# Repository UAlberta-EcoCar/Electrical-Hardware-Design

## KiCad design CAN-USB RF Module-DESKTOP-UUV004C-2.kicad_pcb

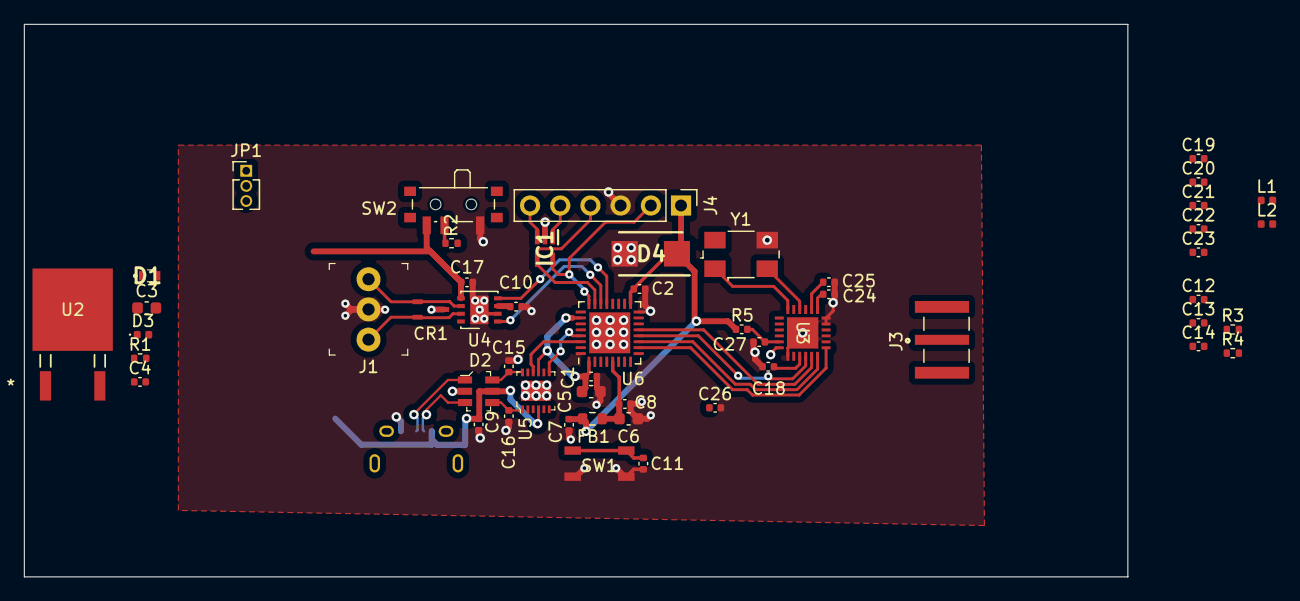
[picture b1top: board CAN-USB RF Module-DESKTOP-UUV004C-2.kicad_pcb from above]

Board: 2 copper layers, 92.8 x 46.5 mm, 54 parts (1 on the bottom side), 32 nets.

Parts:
C1, C2, C4, C9, C10, C11, C12, C14, C17, C18, C27: 100n; C_0402_1005Metric
C3: 22u; C_0603_1608Metric
C5: 10u; C_0603_1608Metric
C6: 1u; C_0603_1608Metric
C7: 1u; C_0402_1005Metric
C8, C24, C25: 10n; C_0402_1005Metric
C13: 4u7; C_0402_1005Metric
C15, C16: 47p; C_0402_1005Metric
C19: 0.8p; C_0402_1005Metric
C20, C23: 1p2; C_0402_1005Metric
C21: 0.5p; C_0402_1005Metric
C22: 100p; C_0402_1005Metric
C26: 470n; C_0402_1005Metric
CR1: ESDCAN03-2BWY; SOT323-3L_STM
D1: ESDA7P120-1U1M; ESDA8P801U1M
D2: USBLC6-2SC6; SOT23-6L
D3: RED; LED_0402_1005Metric
D4: SMLVT3V3; DIOM5436X265N
FB1: 120R; R_0603_1608Metric
IC1: ESDALC6V1W5; SOT65P210X110-5N
J1: 0022232031; PinHeader_1x3_P2.54mm_Drill1.02mm
J2: USB_B_Micro; USB_Micro-B_Amphenol_10118194_Horizontal
J3: Conn_Coaxial; TAOGLAS_EMPCB.SMAFSTJ.B.HT
J4: Conn_01x06_Pin; PinHeader_1x06_P2.54mm_Vertical
JP1: Jumper_3_Bridged12; PinHeader_1x03_P1.27mm_Vertical
L1: 3n; L_0402_1005Metric
L2: 2n5; L_0402_1005Metric
R1: 1k5; R_0402_1005Metric
R2: 10k; R_0402_1005Metric
R3, R4: 27R; R_0402_1005Metric
R5: 0R; C_0402_1005Metric
SW1: RESET; SMD_025816_WRE
SW2: BOOT0; SW_SPDT_PCM12
U2: TLV2217-33KVURG3; KVU3_TEX
U3: SX1280IMLTRT; QFN24_4X4_SEM
U4: MCP2542WFDxMF (CAN); DFN-8-1EP_3x3mm_P0.65mm_EP1.55x2.4mm
U5: FT234XD-R; DFN-12-1EP_3x3mm
U6: STM32L442KCU6; QFN-32-1EP_5x5mm_P0.5mm_EP3.45x3.45mm
Y1: 52MHz; Crystal_SMD_0603-4Pin_6.0x3.5mm

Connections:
+3.3V: C3.1, U2.1 (OUTPUT)
+3.3VA: C6.1, C8.1, FB1.1, U6.5 (VDDA)
+3V3: C1.1, C2.1, C5.1, C7.1, C12.1, C17.2, C18.1, D4.1 (K), FB1.2, IC1.3 (I/02), J4.1, J4.6, R5.2, SW2.3 (C), U3.15 (VBAT), U4.5 (VIO), U5.9 (VCCIO), U6.1 (VDD), U6.17 (VDD), U6.26 (PB3)
+5V: C4.1, C10.2, D1.1 (K), D3.2 (A), JP1.1 (A), JP1.2 (C), U2.3 (INPUT), U4.3 (VDD)
/BOOT0: R2.1, R2.2, SW2.2 (B), U6.31 (PH3)
/CAN Tranciever/CANH+: CR1.2, J1.1, U4.7 (CANH)
/CAN Tranciever/CANL-: CR1.1, J1.3, U4.6 (CANL)
/CAN_RX: U4.4 (RXD), U6.21 (PA11)
/CAN_TX: U4.1 (TXD), U6.22 (PA12)
/DEBUG_JTSK_SWCLK: IC1.5 (I/04), J4.2, U6.24 (PA14)
/DEBUG_JTSK_SWDIO: IC1.4 (I/03), J4.4, U6.23 (PA13)
/LoRa Tranciever/V DIO: C27.1, R5.1, U3.11 (VBAT_IO)
/NRST: C11.2, IC1.1 (I/01), J4.5, SW1.3 (K), SW1.4 (A), U6.4 (NRST)
/SPI1_MISO: U3.16 (MISO_TX), U6.12 (PA6)
/SPI1_MOSI: U3.17 (MOSI_RX), U6.13 (PA7)
/SPI1_NSS: U3.19 (NSS_CTS), U6.10 (PA4)
/SPI1_SCK: U3.18 (SCK_RTSN), U6.11 (PA5)
/UART1_USB_RX: U5.10 (RXD), U6.30 (PB7)
/UART1_USB_TX: U5.7 (TXD), U6.29 (PB6)
/USB Interface/USB_D+: C15.2, D2.1, D2.6, J2.3 (D+), R3.1, R3.2, U5.12 (USBDP)
/USB Interface/USB_D-: C16.2, D2.3, D2.4, J2.2 (D-), R4.1, R4.2, U5.1 (USBDM)
GND: C1.2, C2.2, C3.2, C4.2, C5.2, C6.2, C7.2, C8.2, C9.1, C10.1, C11.1, C12.2, C13.2, C14.2, C15.1, C16.1, C17.1, C18.2, C19.1, C20.2, C23.1, C24.2, C25.2, C26.2, C27.2, CR1.3, D1.2 (A), D2.2, D4.2 (A), IC1.2 (GND), J1.2, J2.5 (GND), J4.3, R1.1, SW1.1, SW1.2, SW2.1 (A), U2.2 (GND), U3.5 (GND), U3.13 (GND), U3.20 (GND), U3.21 (GND), U3.23 (GND), U3.24 (GND), U3.25 (GND), U4.2 (VSS), U4.9 (VSS), U5.5 (GND), U5.13 (GND), U6.16 (VSS), U6.32 (VSS), U6.33 (VSS), Y1.3
unnamed: C20.1, C21.1, L1.2, L2.1
unnamed: C21.2, C22.1, C23.2, L2.2
unnamed: D3.1 (K), R1.2
unnamed: C22.2, J3.1 (In)
unnamed: C25.1, C26.1, U3.2 (VDD_INN), U3.12 (DCC_FB)
unnamed: C19.2, L1.1, U3.22 (RFIO)
unnamed: C24.1, U3.1 (VR_PA)
unnamed: U3.4 (XTA), Y1.2
unnamed: U3.6 (XTB), Y1.1
VBUS: C9.2, C13.1, C14.1, D2.5, J2.1 (VBUS), JP1.3 (B), U5.4 (VCC)

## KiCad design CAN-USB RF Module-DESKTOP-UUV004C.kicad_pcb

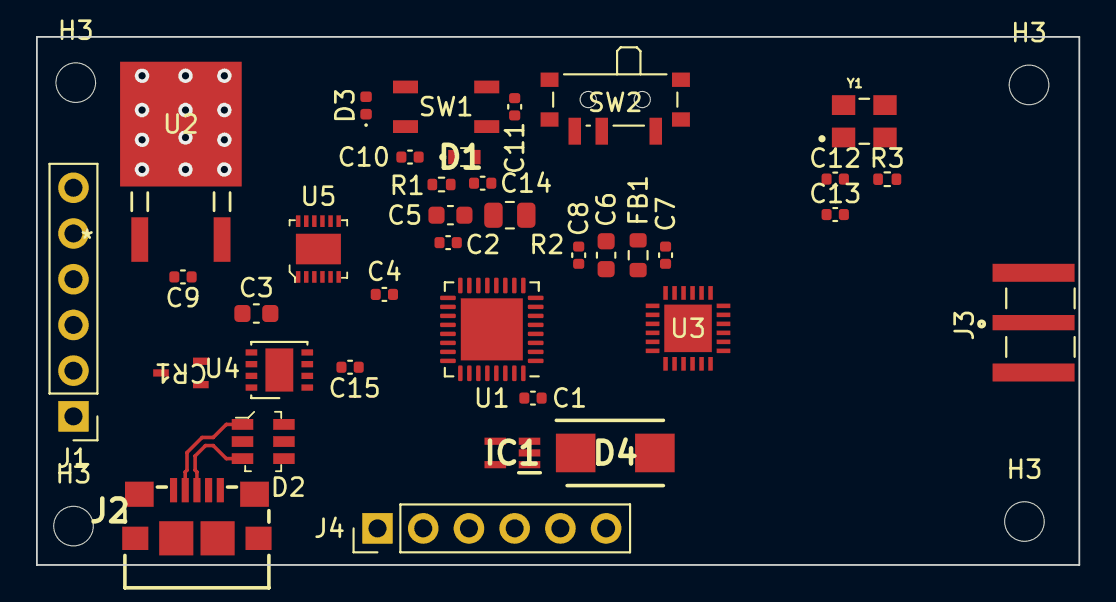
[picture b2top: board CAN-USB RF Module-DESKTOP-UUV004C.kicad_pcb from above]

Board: 2 copper layers, 57.9 x 29.3 mm, 41 parts (0 on the bottom side), 20 nets.

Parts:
C1, C2, C4, C9, C10, C11, C14: 100n; C_0402_1005Metric
C3: 22u; C_0603_1608Metric
C5: 10u; C_0603_1608Metric
C6: 1u; C_0603_1608Metric
C7: 1u; C_0402_1005Metric
C8: 10n; C_0402_1005Metric
C12, C13: 14p; C_0402_1005Metric
C15: 100u; C_0402_1005Metric
CR1: ESDCAN03-2BWY; SOT323-3L_STM
D1: ESDA7P120-1U1M; ESDA8P801U1M
D2: USBLC6-2SC6; SOT23-6L
D3: RED; LED_0402_1005Metric
D4: SMLVT3V3; DIOM5436X265N
FB1: 120R; R_0603_1608Metric
H3, H3#2, H3#3, H3#4: MountingHole; MountingHole_2.2mm_M2_DIN965
IC1: ESDALC6V1W5; SOT65P210X110-5N
J1, J4: Conn_01x06_Pin; PinHeader_1x06_P2.54mm_Vertical
J2: USB_B_Micro; 1981568-1
J3: Conn_Coaxial; TAOGLAS_EMPCB.SMAFSTJ.B.HT
R1: 1k5; R_0402_1005Metric
R2: 10k; R_0805_2012Metric
R3: 390; R_0402_1005Metric
SW1: RESET; SMD_025816_WRE
SW2: BOOT0; SW_SPDT_PCM12
U1: STM32L442KCUx; QFN-32-1EP_5x5mm_P0.5mm_EP3.45x3.45mm
U2: TLV2217-33KVURG3; KVU3_TEX
U3: SX1280IMLTRT; QFN24_4X4_SEM
U4: MCP2542WFDxMF (CAN); DFN-8-1EP_3x3mm_P0.65mm_EP1.55x2.4mm
U5: FT234XD-R; DFN-12-1EP_3x3mm
Y1: 8 MHz; XTAL_ECS-240-8-33-AGN-TR

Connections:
+3.3V: C1.1, C2.1, C3.1, C5.1, C7.1, C15.2, D4.1 (K), FB1.2, J4.1, SW2.3 (C), U1.1 (VDD), U1.17 (VDD), U2.1 (OUTPUT), U4.3 (VDD), U4.5 (VIO)
+3.3VA: C6.1, C8.1, FB1.1, U1.5 (VDDA)
/BOOT0: R2.1, R2.2, SW2.2 (B), U1.31 (PH3)
/CAN_RX: U1.21 (PA11), U4.4 (RXD)
/CAN_TX: U1.22 (PA12), U4.1 (TXD)
/DEBUG_JTDO-SWO: IC1.3 (I/02), J4.6
/DEBUG_JTSK_SWCLK: IC1.5 (I/04), J4.2, U1.24 (PA14)
/DEBUG_JTSK_SWDIO: IC1.4 (I/03), J4.4, U1.23 (PA13)
/NRST: C11.2, IC1.1 (I/01), J4.5, SW1.3 (K), SW1.4 (A), U1.4 (NRST)
/USART1_RX: U1.30 (PB7), U5.10 (RXD)
/USART1_TX: U1.29 (PB6), U5.7 (TXD)
/USB Interface/USB_D+_C: D2.3, J2.3 (D+)
/USB Interface/USB_D-_C: D2.1, J2.2 (D-)
GND: C1.2, C2.2, C3.2, C4.2, C5.2, C6.2, C7.2, C8.2, C9.1, C10.2, C11.1, C12.2, C13.2, C14.1, C15.1, CR1.3, D1.2 (A), D2.2, D4.2 (A), IC1.2 (GND), J1.6, J4.3, R1.1, SW1.1, SW1.2, SW2.1 (A), U1.16 (VSS), U1.32 (VSS), U1.33 (VSS), U2.2 (GND), U4.2 (VSS), U4.9 (VSS), U5.5 (GND), U5.13 (GND), Y1.2, Y1.3
unnamed: C12.1, R3.1, Y1.4
unnamed: D3.1 (K), R1.2
unnamed: CR1.2, J1.2, U4.7 (CANH)
unnamed: CR1.1, J1.4, U4.6 (CANL)
RCC_OSC_IN: C13.1, Y1.1
VBUS: C4.1, C9.2, C10.1, C14.2, D1.1 (K), D2.5, D3.2 (A), J2.4 (ID), U2.3 (INPUT)

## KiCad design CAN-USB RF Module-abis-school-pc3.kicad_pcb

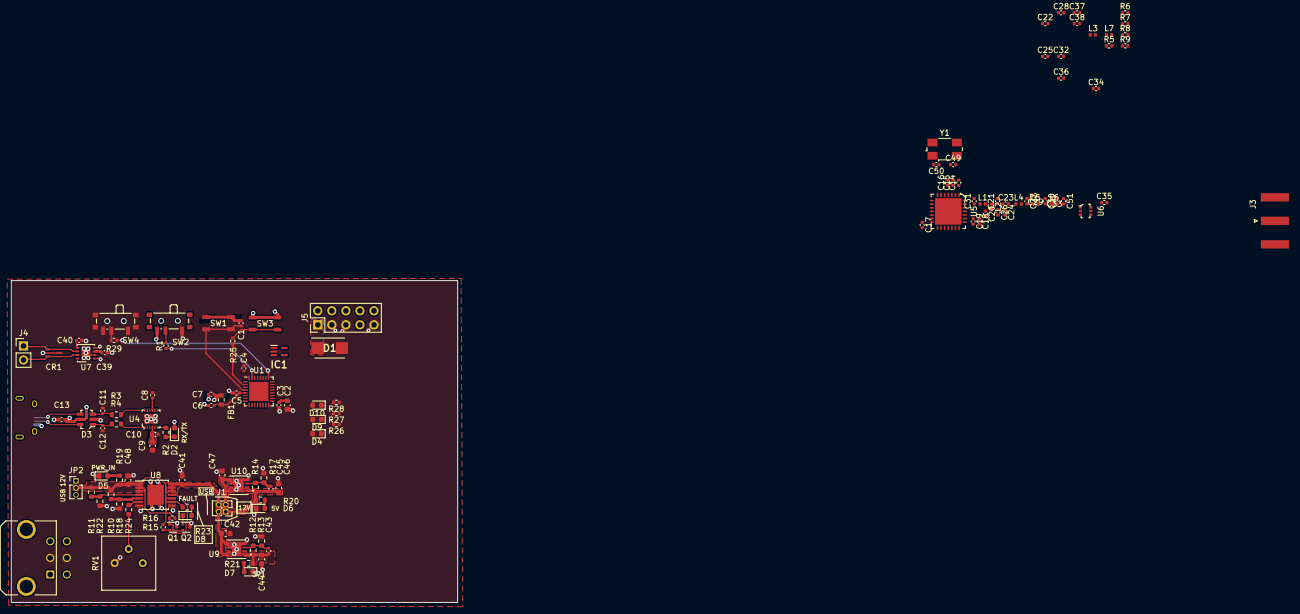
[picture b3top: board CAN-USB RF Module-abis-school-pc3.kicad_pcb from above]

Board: 4 copper layers, 80.6 x 58.2 mm, 123 parts (1 on the bottom side), 81 nets.

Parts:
C1, C3, C4, C8, C10, C13, C14, C15, C16, C17, C19, C39, C40: 100n; C_0402_1005Metric
C2, C48: 10u; C_0603_1608Metric
C5, C20, C31: 10n; C_0402_1005Metric
C6, C7: 1u; C_0402_1005Metric
C9: 4u7; C_0603_1608Metric
C11, C12, C18, C24, C26, C28, C32, C36: 47p; C_0402_1005Metric
C21: 8p2; C_0402_1005Metric
C22, C29, C33, C37, C38, C51: NC; C_0402_1005Metric
C23: 22p; C_0402_1005Metric
C25, C30: 3p3; C_0402_1005Metric
C27: 6p8; C_0402_1005Metric
C34, C35: 1n; C_0402_1005Metric
C41, C42, C47: 1u; C_0603_1608Metric
C43, C45: 10p; C_0402_1005Metric
C44, C46: 2u2; C_0603_1608Metric
C49, C50: 8p; C_0402_1005Metric
CR1: ESDCAN03-2BWY; SOT323-3L_STM
D1: SMLVT3V3; DIOM5436X265N
D2: AMBER RX/TX; LED_0603_1608Metric
D3: USBLC6-2SC6; SOT23-6L
D4, D9: AMBER; LED_0603_1608Metric
D5, D6, D7: BLUE; LED_0603_1608Metric
D8: RED; LED_0603_1608Metric
D10: GREEN; LED_0603_1608Metric
FB1: 120R; R_0603_1608Metric
IC1: ESDALC6V1W5; SOT65P210X110-5N
J1: USB JMPR; PinHeader_2x02_P1.27mm_Vertical
J2: USB_B_Micro; USB_Micro-B_Amphenol_10118194_Horizontal
J3: Conn_Coaxial; SMA_Amphenol_132289_EdgeMount
J4: Conn_01x02_Socket; PinHeader_1x02_P2.54mm_Vertical
J5: Conn_02x05_Top_Bottom; PinHeader_2x05_P2.54mm_Vertical
J6: Fuel Cell Connector; Molex_Micro-Fit_3.0_43045-0621_2x03-1MP_P3.00mm_Horizontal
JP2: Power In; PinHeader_1x03_P1.27mm_Vertical
L1: 1n5; L_0402_1005Metric
L2: 33n; L_0402_1005Metric
L3: 10n; L_0402_1005Metric
L4, L5: 5n6; L_0402_1005Metric
L6, L7: 0H; L_0402_1005Metric
Q1, Q2: NMOS; SOT-523
R1, R15, R16, R25, R26, R27, R28, R29: 10k; R_0402_1005Metric
R2, R21: 260R; R_0603_1608Metric
R3, R4: 27R; R_0603_1608Metric
R5: 0R; R_0402_1005Metric
R6: 100R; R_0402_1005Metric
R7, R9: NC; R_0402_1005Metric
R8: 1k; R_0402_1005Metric
R10, R11: 2M2; R_0603_1608Metric
R12: 500k; R_0603_1608Metric
R13, R17: 160k; R_0603_1608Metric
R14: 845k; R_0603_1608Metric
R18: 225k; R_0603_1608Metric
R19, R20, R23: 600R; R_0603_1608Metric
R22: 800k; R_0603_1608Metric
R24: 10k; R_0603_1608Metric
RV1: SETI; Potentiometer_Bourns_3386P_Vertical
SW1: RESET; SMD_025816_WRE
SW2: BOOT0; SW_SPDT_PCM12
SW3: GPBTN; SMD_025816_WRE
SW4: GPSW; SW_SPDT_PCM12
U1: STM32L442KCU6; QFN-32-1EP_5x5mm_P0.5mm_EP3.45x3.45mm
U4: FT234XD-R; DFN-12-1EP_3x3mm
U5: SX1276IMLTRT; VQFN-28-1EP_6x6mm
U6: P4259-63; SOT-363
U7: MCP2542WFDxMF (CAN); DFN-8-1EP_3x3mm_P0.65mm_EP1.55x2.4mm
U8: MAX14572; TSSOP-14-1EP_4.4x5mm_P0.65mm
U9, U10: TLV76601QWDRBRQ1; TLV76601QWDRBRQ1_TEX
Y1: 32MHz; Crystal_SMD_0603-4Pin_6.0x3.5mm

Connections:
+3.3VA: C5.1, C6.1, FB1.1, U1.5 (VDDA)
+3V3: C2.1, C3.1, C4.1, C7.1, C8.1, C15.1, C17.1, C18.1, C19.1, C34.1, C40.2, C43.1, C44.1, D1.1 (K), D2.2 (A), FB1.2, J5.1, R8.2, R12.1, R21.1, SW2.3 (C), SW3.1, SW3.2, SW4.3 (C), U1.1 (VDD), U1.17 (VDD), U4.9 (VCCIO), U5.3 (VBAT_ANA), U5.14 (VBAT_DIG), U5.24 (VBAT_RF), U6.6 (~CTRL/VDD), U7.5 (VIO), U9.1 (OUT)
+5V: C9.1, C10.1, C39.2, C45.1, C46.1, J1.1, R14.1, R20.1, U4.4 (VCC), U7.3 (VDD), U10.1 (OUT)
+12V: J6.1, J6.4, JP2.3 (B)
/BOOT0: R1.1, R1.2, SW2.2 (B), U1.31 (PH3)
/CAN Tranciever/CANH+: CR1.2, J4.2, U7.7 (CANH)
/CAN Tranciever/CANL-: CR1.1, J4.1, U7.6 (CANL)
/CAN_RX: U1.21 (PA11), U7.4 (RXD)
/CAN_STBY: U1.3 (PC15), U7.8 (STBY)
/CAN_TX: U1.22 (PA12), U7.1 (TXD)
/DEBUG_SWCLK: IC1.4 (I/03), J5.4, U1.24 (PA14)
/DEBUG_SWDIO: IC1.5 (I/04), J5.2, U1.23 (PA13)
/DEBUG_SWO: IC1.3 (I/02), J5.6, U1.26 (PB3)
/DIO0: U1.14 (PB0), U5.8 (DIO0)
/DIO1: U1.15 (PB1), U5.9 (DIO1/DCLK)
/DIO2: U1.29 (PB6), U5.10 (DIO2/DATA)
/DIO3: U1.30 (PB7), U5.11 (DIO3), U5.12 (DIO4), U5.13 (DIO5)
/LoRa Tranciever/RFI_HF: C22.1, L3.1, U5.21 (RFI_HF(GND))
/LoRa Tranciever/RXTX_SW: C35.1, R6.1, R7.1, U6.4 (CTRL)
/LoRa Tranciever/RXTX_SX: R7.2, U5.20 (RXTX/RF_MOD)
/NRST: C1.2, IC1.1 (I/01), J5.10, SW1.3 (K), SW1.4 (A), U1.4 (NRST), U4.2 (RESET#)
/Power Regulator/5V: C42.1, J1.2, U9.5 (EN), U9.8 (IN)
/Power Regulator/12V: C47.1, J1.3, U10.5 (EN), U10.8 (IN)
/Power Regulator/FB: C43.2, C45.2, R12.2, R13.1, R14.2, R17.1, U9.3 (FB), U10.3 (FB)
/Power Regulator/FUSE_IN: C48.1, JP2.2 (C), R10.1, R11.1, R15.1, R16.1, R19.1, R23.1, U8.1 (IN), U8.2 (IN), U8.3 (IN), U8.9 (RIEN), U8.10 (EN)
/Power Regulator/FUSE_OUT: C41.1, J1.4, U8.12 (OUT), U8.13 (OUT), U8.14 (OUT)
/Power Regulator/OVLO: R10.2, R18.1, U8.5 (OVLO)
/Power Regulator/SETI: R24.1, U8.6 (SETI)
/Power Regulator/UVLO: R11.2, R22.1, U8.4 (UVLO)
/Power Regulator/~FLAG: Q1.2 (G), R15.2, U8.11 (~FLAG)
/SPI1_MISO: U1.12 (PA6), U5.17 (MISO)
/SPI1_MOSI: U1.13 (PA7), U5.18 (MOSI)
/SPI1_NSS: U1.10 (PA4), U5.19 (NSS)
/SPI1_SCK: U1.11 (PA5), U5.16 (SCK)
/SW_RXTX: R6.2, R8.1, R9.2, U1.27 (PB4)
/SX_RESET: U1.28 (PB5), U5.7 (NRESET)
/UART2_USB_CTS: U1.6 (PA0), U4.11 (CTS#)
/UART2_USB_RTS: U1.7 (PA1), U4.8 (RTS#)
/UART2_USB_RX: U1.9 (PA3), U4.10 (RXD)
/UART2_USB_TX: U1.8 (PA2), U4.7 (TXD)
/USB Interface/USB_D+: C11.2, D3.3, D3.4, J2.3 (D+), R3.1, R3.2, U4.12 (USBDP)
/USB Interface/USB_D-: C12.2, D3.1, D3.6, J2.2 (D-), R4.1, R4.2, U4.1 (USBDM)
GND: C1.1, C2.2, C3.2, C4.2, C5.2, C6.2, C7.2, C8.2, C9.2, C10.2, C11.1, C12.1, C13.1, C14.2, C15.2, C16.2, C17.2, C18.2, C19.2, C20.2, C21.2, C22.2, C24.2, C25.2, C26.2, C27.1, C30.1, C31.2, C34.2, C35.2, C37.1, C38.1, C39.1, C40.1, C41.2, C42.2, C44.2, C46.2, C47.2, C48.2, C49.2, C50.2, C51.1, CR1.3, D1.2 (A), D3.2, D4.1 (K), D5.1 (K), D6.1 (K), D7.1 (K), D9.1 (K), D10.1 (K), IC1.2 (GND), J2.5 (GND), J3.2 (Ext), J5.3, J5.5, J5.9, J6.2, J6.5, Q1.3 (S), Q2.3 (S), R9.1, R13.2, R17.2, R18.2, R22.2, RV1.3, SW1.1, SW1.2, SW2.1 (A), SW4.1 (A), U1.16 (VSS), U1.32 (VSS), U1.33 (VSS), U4.5 (GND), U4.13 (GND), U5.15 (GND), U5.23 (GND), U5.26 (GND), U5.29 (GND), U6.2 (GND), U7.2 (VSS), U7.9 (VSS), U8.7 (GND), U8.8 (~HVEN), U9.4 (GND), U9.6 (GND), U9.9 (GND), U10.4 (GND), U10.6 (GND), U10.9 (GND), Y1.2, Y1.4
unnamed: C21.1, C23.1, L1.2, L2.1
unnamed: C23.2, L4.1
unnamed: C25.1, C28.1, L3.2
unnamed: C27.2, C29.2, L4.2, L5.1
unnamed: C28.2, R5.1
unnamed: C29.1, C30.2, C33.2, L5.2, L6.1
unnamed: C32.1, R5.2
unnamed: C36.2, C37.2, L7.1
unnamed: D2.1 (K), R2.2
unnamed: D4.2 (A), R28.1
unnamed: D5.2 (A), R19.2
unnamed: D6.2 (A), R20.2
unnamed: D7.2 (A), R21.2
unnamed: D8.2 (A), R23.2
unnamed: D8.1 (K), Q2.1 (D)
unnamed: D9.2 (A), R27.1
unnamed: D10.2 (A), R26.1
unnamed: C38.2, J3.1 (In), L7.2
unnamed: Q1.1 (D), Q2.2 (G), R16.2
unnamed: R24.2, RV1.2
unnamed: R25.1, SW3.3 (K), SW3.4 (A)
unnamed: R29.1, SW4.2 (B)
unnamed: R28.2, U1.18 (PA8)
unnamed: R27.2, U1.19 (PA9)
unnamed: R26.2, U1.20 (PA10)
unnamed: R29.2, U1.25 (PA15)
unnamed: R25.2, U1.2 (PC14)
unnamed: R2.1, U4.6 (CBUS0)
unnamed: C31.1, L1.1, U5.27 (PA_BOOST)
unnamed: C14.1, U5.2 (VR_ANA)
unnamed: C16.1, U5.4 (VR_DIG)
unnamed: C20.1, C24.1, C26.1, L2.2, U5.25 (VR_PA)
unnamed: C49.1, U5.5 (XTA), Y1.3
unnamed: C50.1, U5.6 (XTB), Y1.1
unnamed: C32.2, U6.1 (RF1)
unnamed: C33.1, C51.2, L6.2, U6.3 (RF2)
unnamed: C36.1, U6.5 (RFC)
VBUS_UP: C13.2, D3.5, J2.1 (VBUS), JP2.1 (A)

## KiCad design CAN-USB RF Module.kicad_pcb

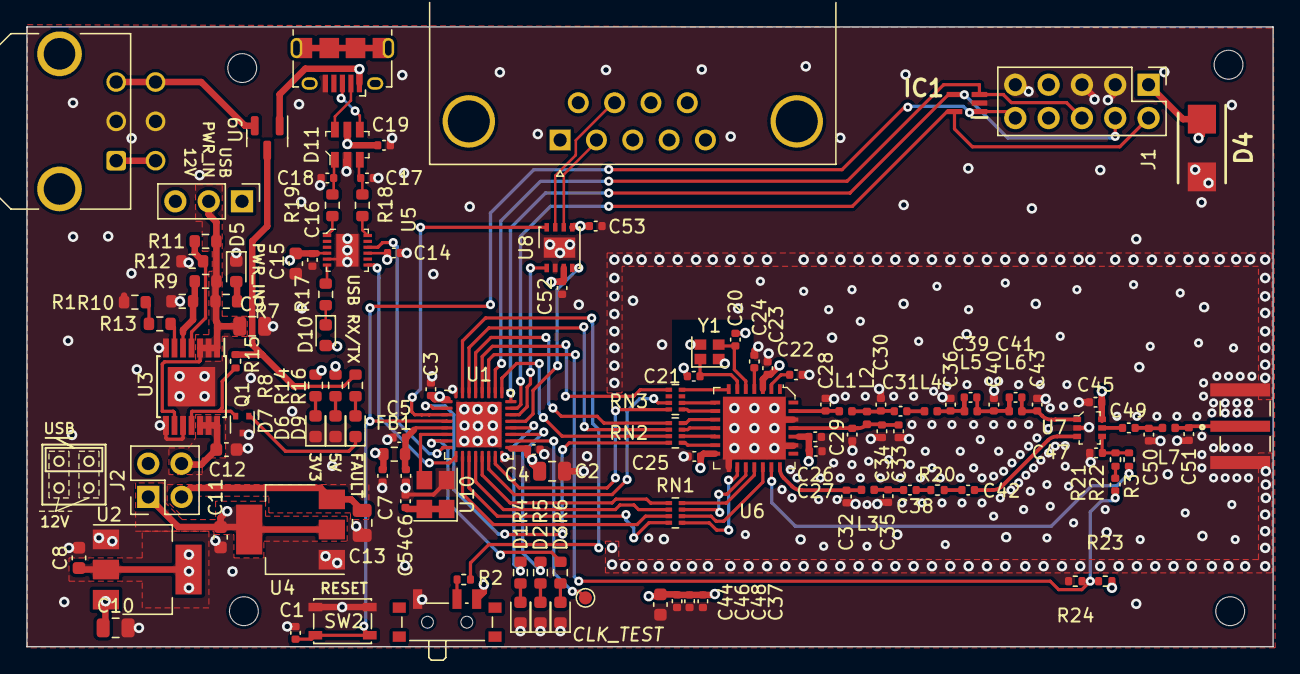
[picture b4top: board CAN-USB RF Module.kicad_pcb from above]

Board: 4 copper layers, 95.0 x 47.2 mm, 126 parts (0 on the bottom side), 91 nets.

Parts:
C1, C3, C4, C14, C16, C19, C22, C23, C24, C25, C27, C52, C53: 100n; C_0402_1005Metric
C2, C9, C10, C13: 10u; C_0805_2012Metric
C5, C28, C29: 10n; C_0402_1005Metric
C6, C7, C37, C46, C48: 1u; C_0402_1005Metric
C8, C11, C44: 22u; C_0603_1608Metric
C12: 1u; C_0603_1608Metric
C15: 4u7; C_0603_1608Metric
C17, C18, C26, C33, C34, C38, C42, C49: 47p; C_0402_1005Metric
C20, C21: 8p; C_0402_1005Metric
C30: 8p2; C_0402_1005Metric
C31: 22p; C_0402_1005Metric
C32, C39, C41, C43, C50, C51: NC; C_0402_1005Metric
C35, C40: 3p3; C_0402_1005Metric
C36: 6p8; C_0402_1005Metric
C45, C47: 1n; C_0402_1005Metric
C54: u1; C_0402_1005Metric
D1: GREEN; LED_0603_1608Metric
D2, D3, D10: AMBER; LED_0603_1608Metric
D4: SMLVT3V3; DIOM5436X265N
D5, D6, D7: BLUE; LED_0603_1608Metric
D9: RED; LED_0603_1608Metric
D11: USBLC6-2SC6; SOT23-6L
FB1: 120R; R_0603_1608Metric
H1, H2, H3, H4: MountingHole; MountingHole_2.2mm_M2
IC1: ESDALC6V1W5; SOT65P210X110-5N
J1: Conn_02x05_Top_Bottom; PinHeader_2x05_P2.54mm_Vertical
J2: USB JMPR; PinHeader_2x02_P2.54mm_Vertical
J3: Fuel Cell Connector; Molex_Micro-Fit_3.0_43045-0621_2x03-1MP_P3.00mm_Horizontal
J4: USB_B_Micro; USB_Micro-B_Amphenol_10118194_Horizontal
J5: Conn_Coaxial; TAOGLAS_EMPCB.SMAFSTJ.B.HT
J6: Conn_01x09_Socket; DSUB-9_Female_Horizontal_P2.77x2.84mm_EdgePinOffset7.70mm_H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
JP1: Power In; PinHeader_1x03_P2.54mm_Vertical
L1: 1n5; L_0402_1005Metric
L2: 33n; L_0402_1005Metric
L3: 10n; L_0402_1005Metric
L4, L5: 5n6; L_0402_1005Metric
L6, L7: 0H; L_0402_1005Metric
Q1: NMOS; SOT-523
R1: 1k5; R_0603_1608Metric
R2, R15: 10k; R_0402_1005Metric
R3: 100R; C_0402_1005Metric
R4, R5, R6: 110R; R_0603_1608Metric
R7, R14, R16: 600R; R_0603_1608Metric
R8, R17: 260R; R_0603_1608Metric
R9, R11: 2M2; R_0603_1608Metric
R10: 225k; R_0603_1608Metric
R12: 800k; R_0603_1608Metric
R13: 10k; R_0603_1608Metric
R18, R19: 27R; R_0603_1608Metric
R20: 0R; R_0402_1005Metric
R21: 100R; R_0402_1005Metric
R22, R24: NC; R_0402_1005Metric
R23: 1k; R_0402_1005Metric
RN1, RN2, RN3: 100R; R_Array_Concave_4x0402
SW2: RESET; SW_SPST_PTS810
SW3: BOOT0; SW_SPDT_PCM12
TP1: CLK_TEST; TestPoint_Pad_D1.0mm
U1: STM32L442KCU6; QFN-32-1EP_5x5mm_P0.5mm_EP3.45x3.45mm
U2: AZ1117-3.3; SOT-223-3_TabPin2
U3: MAX14572; TSSOP-14-1EP_4.4x5mm_P0.65mm
U4: AZ1117-5.0; SOT-223-3_TabPin2
U5: FT234XD-R; DFN-12-1EP_3x3mm
U6: SX1276IMLTRT; VQFN-28-1EP_6x6mm
U7: P4259-63; SOT-363
U8: MCP2542FDxMF; DFN-8-1EP_3x3mm_P0.65mm_EP1.55x2.4mm
U9: Common Cathode SBD; SOT-23
U10: 8MHz; Crystal_SMD_3225-4Pin_3.2x2.5mm
Y1: 32MHz; Crystal_SMD_2016-4Pin_2.0x1.6mm

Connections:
+3.3VA: C5.1, C6.1, FB1.1, U1.5 (VDDA)
+3V3: C2.1, C3.1, C4.1, C7.1, C8.1, C14.1, C23.1, C25.1, C26.1, C27.1, C37.1, C44.1, C45.1, C46.1, C48.1, C53.2, C54.2, D4.1 (K), D10.2 (A), FB1.2, J1.1, R8.1, R23.2, SW3.3 (C), U1.1 (VDD), U1.17 (VDD), U2.2 (VO), U5.9 (VCCIO), U6.3 (VBAT_ANA), U6.14 (VBAT_DIG), U6.24 (VBAT_RF), U7.6 (~CTRL/VDD), U8.5 (VIO), U10.1 (~ST), U10.4 (VCC)
+5V: C11.1, C15.1, C16.1, C52.2, J2.1, R14.1, U4.2 (VO), U5.4 (VCC), U8.3 (VDD)
+12V: J3.1, J3.4, JP1.3 (B)
/BOOT0: R2.1, R2.2, SW3.2 (B), U1.31 (PH3)
/CAN Tranciever/CD+: J6.7, U8.7 (CANH)
/CAN Tranciever/CD-: J6.2, U8.6 (CANL)
/CAN_RX: U1.21 (PA11), U8.4 (RXD)
/CAN_STBY: U1.3 (PC15), U8.8 (STBY)
/CAN_TX: U1.22 (PA12), U8.1 (TXD)
/DEBUG_SWCLK: IC1.4 (I/03), J1.4, U1.24 (PA14)
/DEBUG_SWDIO: IC1.5 (I/04), J1.2, U1.23 (PA13)
/DEBUG_SWO: IC1.3 (I/02), J1.6, U1.26 (PB3)
/DIO0: RN3.3 (R3.1), U1.14 (PB0)
/DIO1: RN3.4 (R4.1), U1.15 (PB1)
/DIO2: RN2.1 (R1.1), U1.29 (PB6)
/DIO3: RN2.2 (R2.1), U1.30 (PB7)
/DIO4: RN2.3 (R3.1), U1.25 (PA15)
/DIO5: RN2.4 (R4.1), U1.2 (PC14)
/LoRa Tranciever/DIO0: RN3.6 (R3.2), U6.8 (DIO0)
/LoRa Tranciever/DIO1: RN3.5 (R4.2), U6.9 (DIO1/DCLK)
/LoRa Tranciever/DIO2: RN2.8 (R1.2), U6.10 (DIO2/DATA)
/LoRa Tranciever/DIO3: RN2.7 (R2.2), U6.11 (DIO3)
/LoRa Tranciever/DIO4: RN2.6 (R3.2), U6.12 (DIO4)
/LoRa Tranciever/DIO5: RN2.5 (R4.2), U6.13 (DIO5)
/LoRa Tranciever/MISO_TX: RN1.7 (R2.2), U6.17 (MISO)
/LoRa Tranciever/MOSI_RX: RN1.8 (R1.2), U6.18 (MOSI)
/LoRa Tranciever/NSS_CTS: RN1.6 (R3.2), U6.19 (NSS)
/LoRa Tranciever/RFI_HF: C32.1, L3.1, U6.21 (RFI_HF(GND))
/LoRa Tranciever/RFO_HF: C28.1, L1.1, U6.27 (PA_BOOST)
/LoRa Tranciever/RXTX_EXT: R3.1, R21.2, R23.1, R24.2
/LoRa Tranciever/RXTX_SW: C47.1, R21.1, R22.1, U7.4 (CTRL)
/LoRa Tranciever/RXTX_SX: R22.2, U6.20 (RXTX/RF_MOD)
/LoRa Tranciever/SCK_RTSN: RN1.5 (R4.2), U6.16 (SCK)
/LoRa Tranciever/SX1276_NRESET: RN3.8 (R1.2), U6.7 (NRESET)
/NRST: C1.2, IC1.1 (I/01), J1.10, SW2.2, U1.4 (NRST)
/Power Regulator/5V: C10.1, J2.2, U2.3 (VI)
/Power Regulator/5V_UP: J3.3, J3.6, U9.2
/Power Regulator/12V: C13.1, J2.3, U4.3 (VI)
/Power Regulator/FUSE_IN: C9.1, JP1.2 (C), R7.1, R9.1, R11.1, U3.1 (IN), U3.2 (IN), U3.3 (IN), U3.9 (RIEN)
/Power Regulator/FUSE_OUT: C12.1, J2.4, U3.12 (OUT), U3.13 (OUT), U3.14 (OUT)
/Power Regulator/OVLO: R9.2, R10.1, U3.5 (OVLO)
/Power Regulator/SETI: R13.1, U3.6 (SETI)
/Power Regulator/UVLO: R11.2, R12.1, U3.4 (UVLO)
/Power Regulator/~FLAG: Q1.2 (G), R15.2, U3.11 (~FLAG)
/SPI1_MISO: RN1.2 (R2.1), U1.12 (PA6)
/SPI1_MOSI: RN1.1 (R1.1), U1.13 (PA7)
/SPI1_NSS: RN1.3 (R3.1), U1.10 (PA4)
/SPI1_SCK: RN1.4 (R4.1), U1.11 (PA5)
/SW_RXTX: R3.2, U1.27 (PB4)
/SX_RESET: RN3.1 (R1.1), U1.28 (PB5)
/UART2_USB_RX: U1.9 (PA3), U5.7 (TXD)
/UART2_USB_TX: U1.8 (PA2), U5.10 (RXD)
/USB Interface/USB_D+: C17.2, D11.3, D11.4, J4.3 (D+), R18.1, R18.2, U5.12 (USBDP)
/USB Interface/USB_D-: C18.2, D11.1, D11.6, J4.2 (D-), R19.1, R19.2, U5.1 (USBDM)
/XCLK: U1.6 (PA0), U10.3 (OUT)
GND: C1.1, C2.2, C3.2, C4.2, C5.2, C6.2, C7.2, C8.2, C9.2, C10.2, C11.2, C12.2, C13.2, C14.2, C15.2, C16.2, C17.1, C18.1, C19.1, C20.2, C21.2, C22.2, C23.2, C24.2, C25.2, C26.2, C27.2, C28.2, C29.2, C30.2, C32.2, C33.2, C34.2, C35.2, C36.1, C37.2, C40.1, C43.1, C44.2, C45.2, C46.2, C47.2, C48.2, C50.1, C51.1, C52.1, C53.1, C54.1, D1.1 (K), D2.1 (K), D3.1 (K), D4.2 (A), D5.1 (K), D6.1 (K), D7.1 (K), D11.2, IC1.2 (GND), J1.3, J1.5, J1.9, J3.2, J3.5, J4.5 (GND), J5.2 (Ext), Q1.3 (S), R1.2, R10.2, R12.2, R24.1, SW2.1, SW3.1 (A), U1.16 (VSS), U1.32 (VSS), U1.33 (VSS), U2.1 (GND), U3.7 (GND), U3.8 (~HVEN), U3.10 (EN), U3.15 (GND), U4.1 (GND), U5.5 (GND), U5.13 (GND), U6.15 (GND), U6.23 (GND), U6.26 (GND), U6.29 (GND), U7.2 (GND), U8.2 (VSS), U8.9 (VSS), U10.2 (GND), Y1.2, Y1.4
unnamed: C30.1, C31.1, L1.2, L2.1
unnamed: C31.2, L4.1
unnamed: C35.1, C38.1, L3.2
unnamed: C36.2, C39.2, L4.2, L5.1
unnamed: C38.2, R20.1
unnamed: C39.1, C40.2, C41.2, L5.2, L6.1
unnamed: C42.1, R20.2
unnamed: C49.2, C50.2, L7.1
unnamed: D1.2 (A), R4.1
unnamed: D2.2 (A), R5.1
unnamed: D3.2 (A), R6.1
unnamed: D5.2 (A), R7.2
unnamed: D6.2 (A), R8.2
unnamed: D7.2 (A), R14.2
unnamed: D9.2 (A), R16.2
unnamed: D9.1 (K), Q1.1 (D)
unnamed: D10.1 (K), R17.2
unnamed: C51.2, J5.1 (In), L7.2
unnamed: R1.1, R13.2
unnamed: R15.1, R16.1, U9.3
unnamed: R6.2, U1.7 (PA1)
unnamed: TP1.1, U1.18 (PA8)
unnamed: R5.2, U1.19 (PA9)
unnamed: R4.2, U1.20 (PA10)
unnamed: R17.1, U5.6 (CBUS0)
unnamed: C22.1, U6.2 (VR_ANA)
unnamed: C24.1, U6.4 (VR_DIG)
unnamed: C29.1, C33.1, C34.1, L2.2, U6.25 (VR_PA)
unnamed: C20.1, U6.5 (XTA), Y1.3
unnamed: C21.1, U6.6 (XTB), Y1.1
unnamed: C41.1, C43.2, L6.2, U7.1 (RF1)
unnamed: C42.2, U7.3 (RF2)
unnamed: C49.1, U7.5 (RFC)
VBUS_UP: C19.2, D11.5, J4.1 (VBUS), JP1.1 (A), U9.1

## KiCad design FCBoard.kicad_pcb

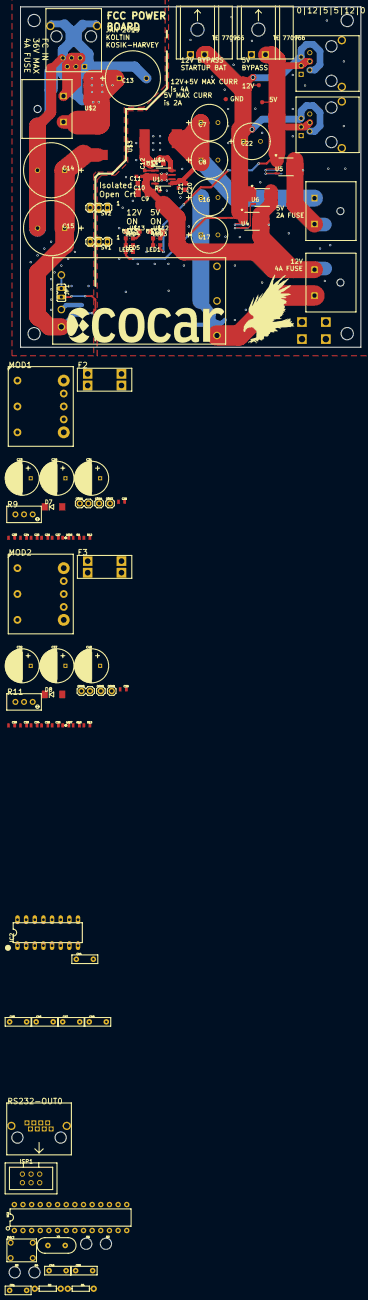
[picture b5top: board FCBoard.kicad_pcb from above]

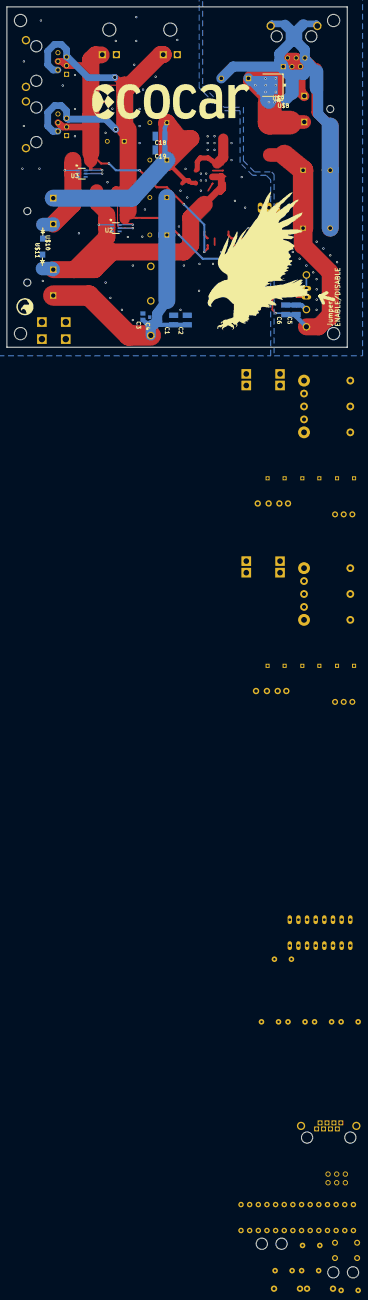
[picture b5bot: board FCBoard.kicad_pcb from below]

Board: 2 copper layers, 100.0 x 100.0 mm, 126 parts (17 on the bottom side), 49 nets.

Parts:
@HOLE0, @HOLE1, @HOLE2, @HOLE3: (no value)
C1, C2, C9, C18, C19: 10uF; C1210
C3, C10, C20: 1uF; C0805
C4, C11, C12, C21: 0.1uF; C0603
C5, C6: 1uF; C1210
C7, C8, C16, C17, C22: EEUFR1H221B; CAP_PAN_10X16
C13, C14, C15: EEU-FC2A221; CAP_16_X_25
C23, C28, C31, C32, C37, C40: 220uF; CAPACITOR_220UF_63V
C24, C33: 0.1uF; 0805
C25, C26, C27, C34, C35, C36: 10uF; 0805
C29, C38: 1nF/50V; 0805
C30, C39: 1uF/50V; 0805
C44, C45, C46, C47, C48: 1uF; CAP-PTH-5MM
C49: 0.1uF; CAP-PTH-5MM
C50, C51: 22pF; CAP-PTH-5MM
CON4, CON5, CON7, CON9: 1X01
CON6, CON8: 1X02
D7: SMBJ12A; DO214AA
D8: SMBJ5.0A; DO214AA
E1, E2, E3: 5555140-6; 1734723-1_RJ11
F2, F3: 7.5A; FUSEHOLDER_VERTICAL
H1, H2, H3, H4: STAND-OFF
IC2: RS232-TTL_MAX232E; DIP16
ISP1: ISP; ISP_CONNECTOR
JP1: JP1
LED1: Amber 1.9V; CHIPLED_0805
LED2: Blue 3.3V; CHIPLED_0805
LED3, LED4, LED5: CHIPLED_0805
LED6, LED7: RED; 0805_LED
MOD1, MOD2: i3A; CONVERTER_I3A
PB2: PUSHBUTTON
R1: R0603
R3: 10k; AXIAL-0.3
R4: 0; AXIAL-0.3
R8: 1.6k; 0805
R9, R11: 10k; TRIMPOT
R10: 8.2k; 0805
R12: 2k; 0805
R13: 560; 0805
RS232-OUT0: RJ45
SV1, SV2: MA03-1
TP1, TP2, TP3: TEST-POINT3X5; PAD.03X.05
U1: ADP2302ARDZ-5.0-R7; RD_8_1
U2, U3: LTC4412HVIS6TRMPBF; TSOT-23_S6
U4, U5, U6: SI9433BDY-T1-E3; SOIC-N-8_SI
U$1: RPA60-2412SFW_P
U$2: 47uH; INDUCTOR_SMD_FOOTPRINT
U$3: 744770112; INDUCTOR_SMD_FOOTPRINT
U$4: DB2460500L; SOD123
U$5, U$6, U$7: SHELL2013_FUSEMINI-BLADE; SHELL2013_MINI-BLADE-FUSE
U$8: P4SMA51A; SMA-DO214AC
U$9: VS-15EWL06FNTR-M3; TO252
U$10: SMAJ12A; SMA-DO214AC
U$11: SMAJ5.0A; SMA-DO214AC
U$12, U$13: NSI45020AT1G; SOD123
U$14, U$15: ECOCAR_LOGO_2018
U$16: CS-2016-LOGO-5MM
U$17: EAGLE-PLC-30MM
U$18, U$20: 2X1-CONN; 2X1-MATE-N-LOCK
U$19: EAGLE-PLC-15MM
U$21: M3_SCREW_TERMINAL
UC2: 328P; DIP28
Y2: 16MHz; HC49US

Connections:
5V: C44.2, C45.1, C49.1, D8.C, E2.3, E2.4, E3.3, E3.4, F3.3, F3.4, IC2.16, LED1.A, LED7.1, R3.P$2, R4.P$1, TP2.P$1, U3.6, U5.1, U5.2, U5.3, U$18.CIRCUIT1, UC2.7, UC2.20, UC2.21
5V_PRE_FUSE: C32.+, C33.1, C34.1, C35.1, C36.1, C37.+, CON5.1, F3.1, F3.2, MOD2.7, MOD2.8
5V_U: U3.1, U5.5, U5.6, U5.7, U5.8, U$5.OUT, U$11.K
12V: C22.1, D7.C, E2.2, E2.5, E3.2, E3.5, F2.3, F2.4, LED5.A, LED6.1, TP1.P$1, U2.6, U4.1, U4.2, U4.3, U6.1, U6.2, U6.3, U$20.CIRCUIT1
12V_PRE_FUSE: C23.+, C24.1, C25.1, C26.1, C27.1, C28.+, CON4.1, F2.1, F2.2, MOD1.7, MOD1.8
12V_REG: C1.1, C2.1, C3.1, C4.1, C16.1, C17.1, U$1.P$6, U$7.OUT
12V_U: C9.1, C10.1, C11.1, R1.1, U1.2, U1.3, U2.1, U4.5, U4.6, U4.7, U4.8, U6.5, U6.6, U6.7, U6.8, U$7.IN, U$10.K
FCC_IN: E1.2, E1.3, E1.4, E1.5, U$6.OUT
FEEDBACK: C7.1, C8.1, C18.1, C19.1, C20.1, C21.1, U1.5, U$3.1, U$5.IN
GATE_5V: U3.5, U5.4
GATE_12V: U2.5, U4.4, U6.4
GND: C1.2, C2.2, C3.2, C4.2, C7.2, C8.2, C9.2, C10.2, C11.2, C16.2, C17.2, C18.2, C19.2, C20.2, C21.2, C22.2, C23.-, C24.2, C25.2, C26.2, C27.2, C28.-, C29.2, C30.2, C31.-, C32.-, C33.2, C34.2, C35.2, C36.2, C37.-, C38.2, C39.2, C40.-, C45.2, C48.1, C49.2, C50.2, C51.2, CON6.1, CON7.1, CON8.1, CON9.1, D7.A, D8.A, E2.1, E2.6, E2.SH1, E2.SH2, E3.1, E3.6, E3.SH1, E3.SH2, IC2.15, ISP1.6, MOD1.3, MOD1.4, MOD2.3, MOD2.4, PB2.3, PB2.4, R9.3, R11.3, R12.1, R13.1, RS232-OUT0.4, RS232-OUT0.5, RS232-OUT0.9, RS232-OUT0.10, SV1.1, SV1.2, SV2.1, SV2.2, TP3.P$1, U1.6, U1.7, U1.EPAD, U2.2, U2.3, U3.2, U3.3, U$1.P$5, U$4.A, U$10.A, U$11.A, U$12.C, U$13.C, U$18.GND, U$20.GND, U$21.P$1, U$21.P$2, U$21.P$3, U$21.P$4, UC2.8, UC2.22
GND_IN: C5.2, C6.2, C13.2, C14.2, C15.2, E1.1, E1.6, E1.SH1, E1.SH2, SV1.3, SV2.3, U$1.P$2, U$8.A, U$9.1, U$9.2
MISO: ISP1.1, UC2.18
MOSI: ISP1.4, UC2.17
unnamed: JP1.1, U$1.P$3
unnamed: MOD1.6, R8.1
unnamed: C12.1, U1.1
unnamed: C12.2, U1.8, U$3.2, U$4.C
unnamed: R1.2, U1.4
unnamed: R8.2, R9.1, R9.2
unnamed: LED1.C, LED3.A
unnamed: LED3.C, U$12.A
unnamed: LED4.C, U$13.A
unnamed: LED2.C, LED4.A
unnamed: LED2.A, LED5.C
unnamed: C5.1, C6.1, C14.1, C15.1, JP1.2, U$1.P$1, U$2.1
unnamed: LED7.2, R13.2
unnamed: MOD2.6, R10.1
unnamed: LED6.2, R12.2
unnamed: C50.1, UC2.9, Y2.2
unnamed: C51.1, UC2.10, Y2.1
unnamed: ISP1.2, R4.P$2
unnamed: C44.1, IC2.2
unnamed: C46.2, IC2.1
unnamed: C46.1, IC2.3
unnamed: C47.2, IC2.4
unnamed: R10.2, R11.1, R11.2
unnamed: C47.1, IC2.5
unnamed: C48.2, IC2.6
unnamed: CON6.2, MOD1.2
unnamed: CON8.2, MOD2.2
RESET: ISP1.5, PB2.1, PB2.2, R3.P$1, UC2.1
RX_OUT_RS232: IC2.8, RS232-OUT0.6
RX_OUT_TTL: IC2.9, UC2.24
SCK: ISP1.3, UC2.19
TX_OUT_RS232: IC2.7, RS232-OUT0.3
TX_OUT_TTL: IC2.10, UC2.23
VIN: C13.1, C29.1, C30.1, C31.+, C38.1, C39.1, C40.+, MOD1.1, MOD2.1, U$2.2, U$6.IN, U$8.K, U$9.3
